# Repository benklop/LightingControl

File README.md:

# LightingControl

Welcome to your new gem! In this directory, you'll find the files you need to be able to package up your Ruby library into a gem. Put your Ruby code in the file `lib/LightingControl`. To experiment with that code, run `bin/console` for an interactive prompt.

TODO: Delete this and the text above, and describe your gem

## Installation

Add this line to your application's Gemfile:

```ruby
gem 'LightingControl'
```

And then execute:

    $ bundle

Or install it yourself as:

    $ gem install LightingControl

## Usage

TODO: Write usage instructions here

## Development

After checking out the repo, run `bin/setup` to install dependencies. You can also run `bin/console` for an interactive prompt that will allow you to experiment.

To install this gem onto your local machine, run `bundle exec rake install`. To release a new version, update the version number in `version.rb`, and then run `bundle exec rake release`, which will create a git tag for the version, push git commits and tags, and push the `.gem` file to [rubygems.org](https://rubygems.org).

## Contributing

Bug reports and pull requests are welcome on GitHub at https://github.com/[USERNAME]/LightingControl.

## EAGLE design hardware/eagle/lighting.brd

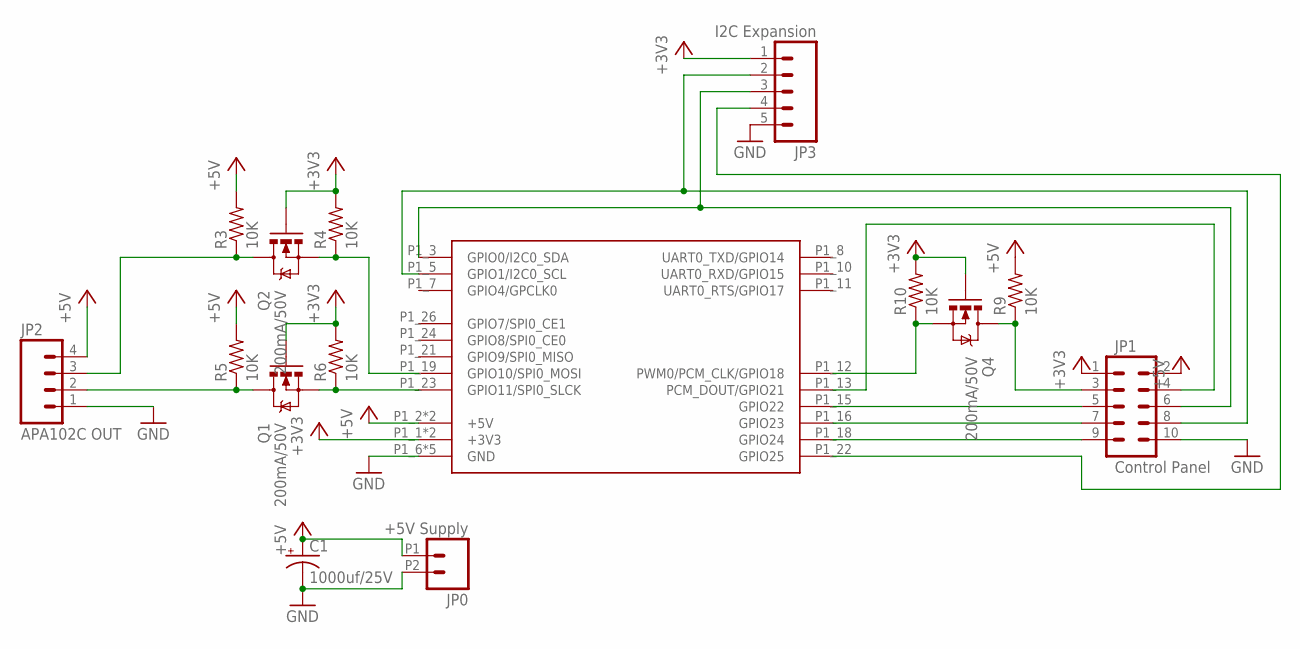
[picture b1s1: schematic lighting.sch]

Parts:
C1: 1000uf/25V; CPOL-RADIAL-1000UF-25V-KIT
JP0: +5V Supply; 1X02_2.54_SCREWTERM
JP1: Control Panel; 2X5-SHROUDED_LOCK
JP2: APA102C OUT; MOLEX-1X4_LOCK
JP3: I2C Expansion; 1X05_LOCK
Q1, Q2, Q4: 200mA/50V; SOT23-3
R3, R4, R5, R6, R9, R10: 10K; 0603-RES
U$1: RPI-B-V1

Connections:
+3V3: JP1.1, JP3.1, Q1.1 (G), Q2.1 (G), Q4.1 (G), R4.2, R6.2, R10.2, U$1.P1_1 (+3V3), U$1.P1_17 (+3V3)
+5V: C1.+, JP0.P1 (1), JP1.2, JP2.4, R3.2, R5.2, R9.2, U$1.P1_2 (+5V), U$1.P1_4 (+5V)
GND: C1.-, JP0.P2 (2), JP1.10, JP2.1, JP3.5, U$1.P1_6 (GND), U$1.P1_9 (GND), U$1.P1_14 (GND), U$1.P1_20 (GND), U$1.P1_25 (GND)
unnamed: Q2.2 (S), R4.1, U$1.P1_19 (GPIO10/SPI0_MOSI)
unnamed: JP1.5, U$1.P1_15 (GPIO22)
unnamed: JP1.7, U$1.P1_16 (GPIO23)
unnamed: JP1.9, U$1.P1_18 (GPIO24)
unnamed: JP1.6, JP3.3, U$1.P1_3 (GPIO0/I2C0_SDA)
unnamed: JP1.8, JP3.2, U$1.P1_5 (GPIO1/I2C0_SCL)
unnamed: Q1.2 (S), R6.1, U$1.P1_23 (GPIO11/SPI0_SLCK)
unnamed: JP3.4, U$1.P1_22 (GPIO25)
unnamed: JP2.3, Q2.3 (D), R3.1
unnamed: JP2.2, Q1.3 (D), R5.1
unnamed: JP1.4, U$1.P1_13 (PCM_DOUT/GPIO21)
unnamed: JP1.3, Q4.3 (D), R9.1
unnamed: Q4.2 (S), R10.1, U$1.P1_12 (PWM0/PCM_CLK/GPIO18)

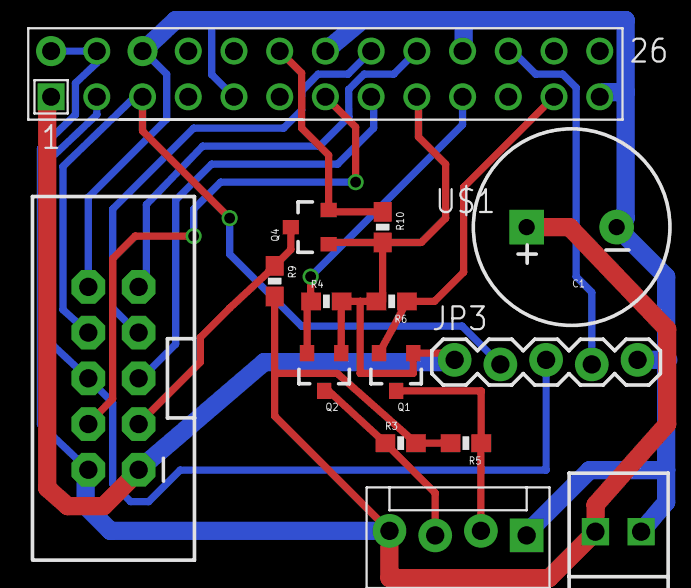
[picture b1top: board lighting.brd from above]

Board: 2 copper layers, 15 parts (0 on the bottom side), 16 nets.

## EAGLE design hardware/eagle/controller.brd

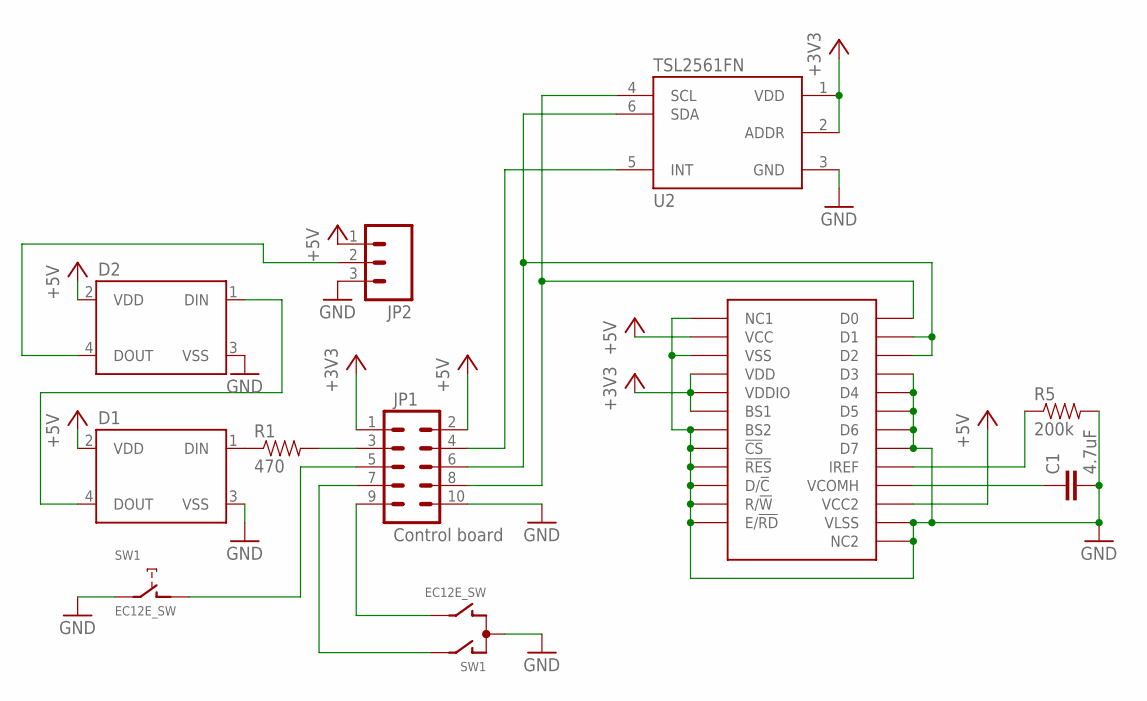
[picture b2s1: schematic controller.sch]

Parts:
C1: 4.7uF; 1206-CAP
D1, D2: WS2812BTHRU; APA-106-F5
JP1: Control board; 2X5-SHROUDED_LOCK
JP2: M03LOCK; 1X03_LOCK
R1: 470; 0603-RES
R5: 200k; 0603-RES
SW1: EC12E_SW; ALPS_EC12E_SW
U2: TSL2561FN; FN-6
U$1: ER-OLED011

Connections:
+3V3: JP1.1, U2.1 (VDD), U2.2 (ADDR), U$1.BS1, U$1.VDD, U$1.VDDIO
+5V: D1.2 (VDD), D2.2 (VDD), JP1.2, JP2.1, U$1.VCC, U$1.VCC2
GND: C1.2, D1.3 (VSS), D2.3 (VSS), JP1.10, JP2.3, R5.2, SW1.C, SW1.E (2), U2.3 (GND), U$1.!CS, U$1.!RES, U$1.BS2, U$1.D3, U$1.D4, U$1.D5, U$1.D6, U$1.D7, U$1.D/!C, U$1.E/!RD, U$1.NC1, U$1.NC2, U$1.R/!W, U$1.VLSS, U$1.VSS
unnamed: D1.1 (DIN), R1.1
unnamed: D1.4 (DOUT), D2.1 (DIN)
unnamed: JP1.3, R1.2
unnamed: D2.4 (DOUT), JP2.2
unnamed: JP1.4, U2.5 (INT)
unnamed: JP1.7, SW1.A
unnamed: JP1.9, SW1.B
unnamed: JP1.5, SW1.D (1)
unnamed: R5.1, U$1.IREF
unnamed: C1.1, U$1.VCOMH
unnamed: JP1.6, U2.6 (SDA), U$1.D1, U$1.D2
unnamed: JP1.8, U2.4 (SCL), U$1.D0

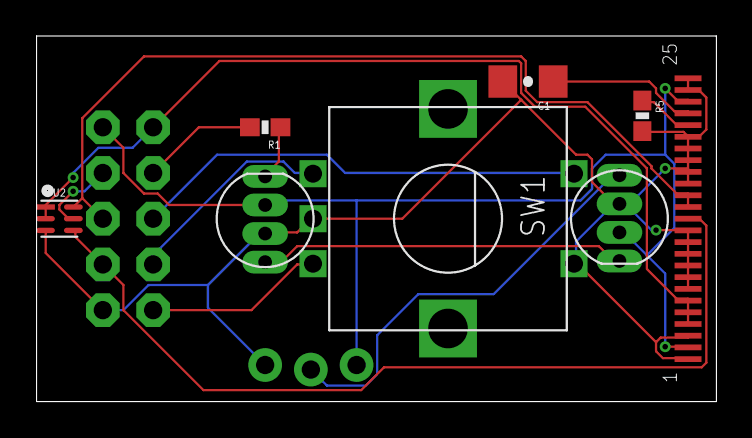
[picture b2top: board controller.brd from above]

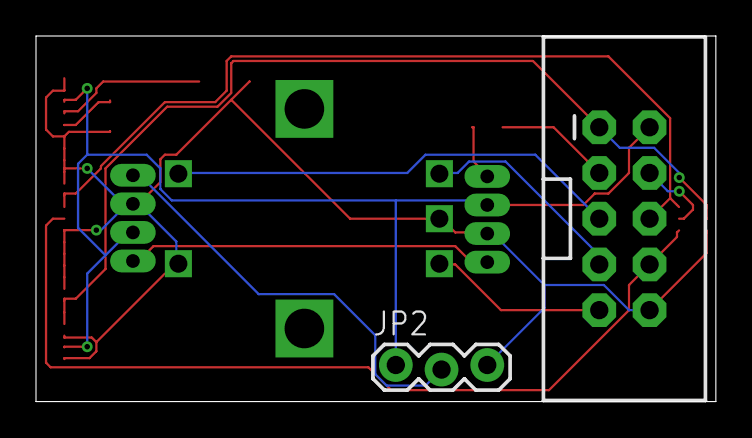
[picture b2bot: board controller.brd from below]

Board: 2 copper layers, 37.8 x 20.3 mm, 10 parts (2 on the bottom side), 15 nets.

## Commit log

2016-01-10 add gem files
2016-01-12 initial playing around
2016-01-13 modularize
2016-01-13 move notify / yield to the end so it does not interfere with timers
2016-01-13 add hardware files

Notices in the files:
parts and their libraries:
SparkFun-Capacitors: Licensing: Creative Commons ShareAlike 4.0 International - https://creativecommons.org/licenses/by-sa/4.0
raspberry: This library stands under the CERN Open Hardware Licence.
